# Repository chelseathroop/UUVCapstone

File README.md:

# UUVCapstone
Repository for acoustic recording device for UUV Capstone project 2015 at Portland State University.

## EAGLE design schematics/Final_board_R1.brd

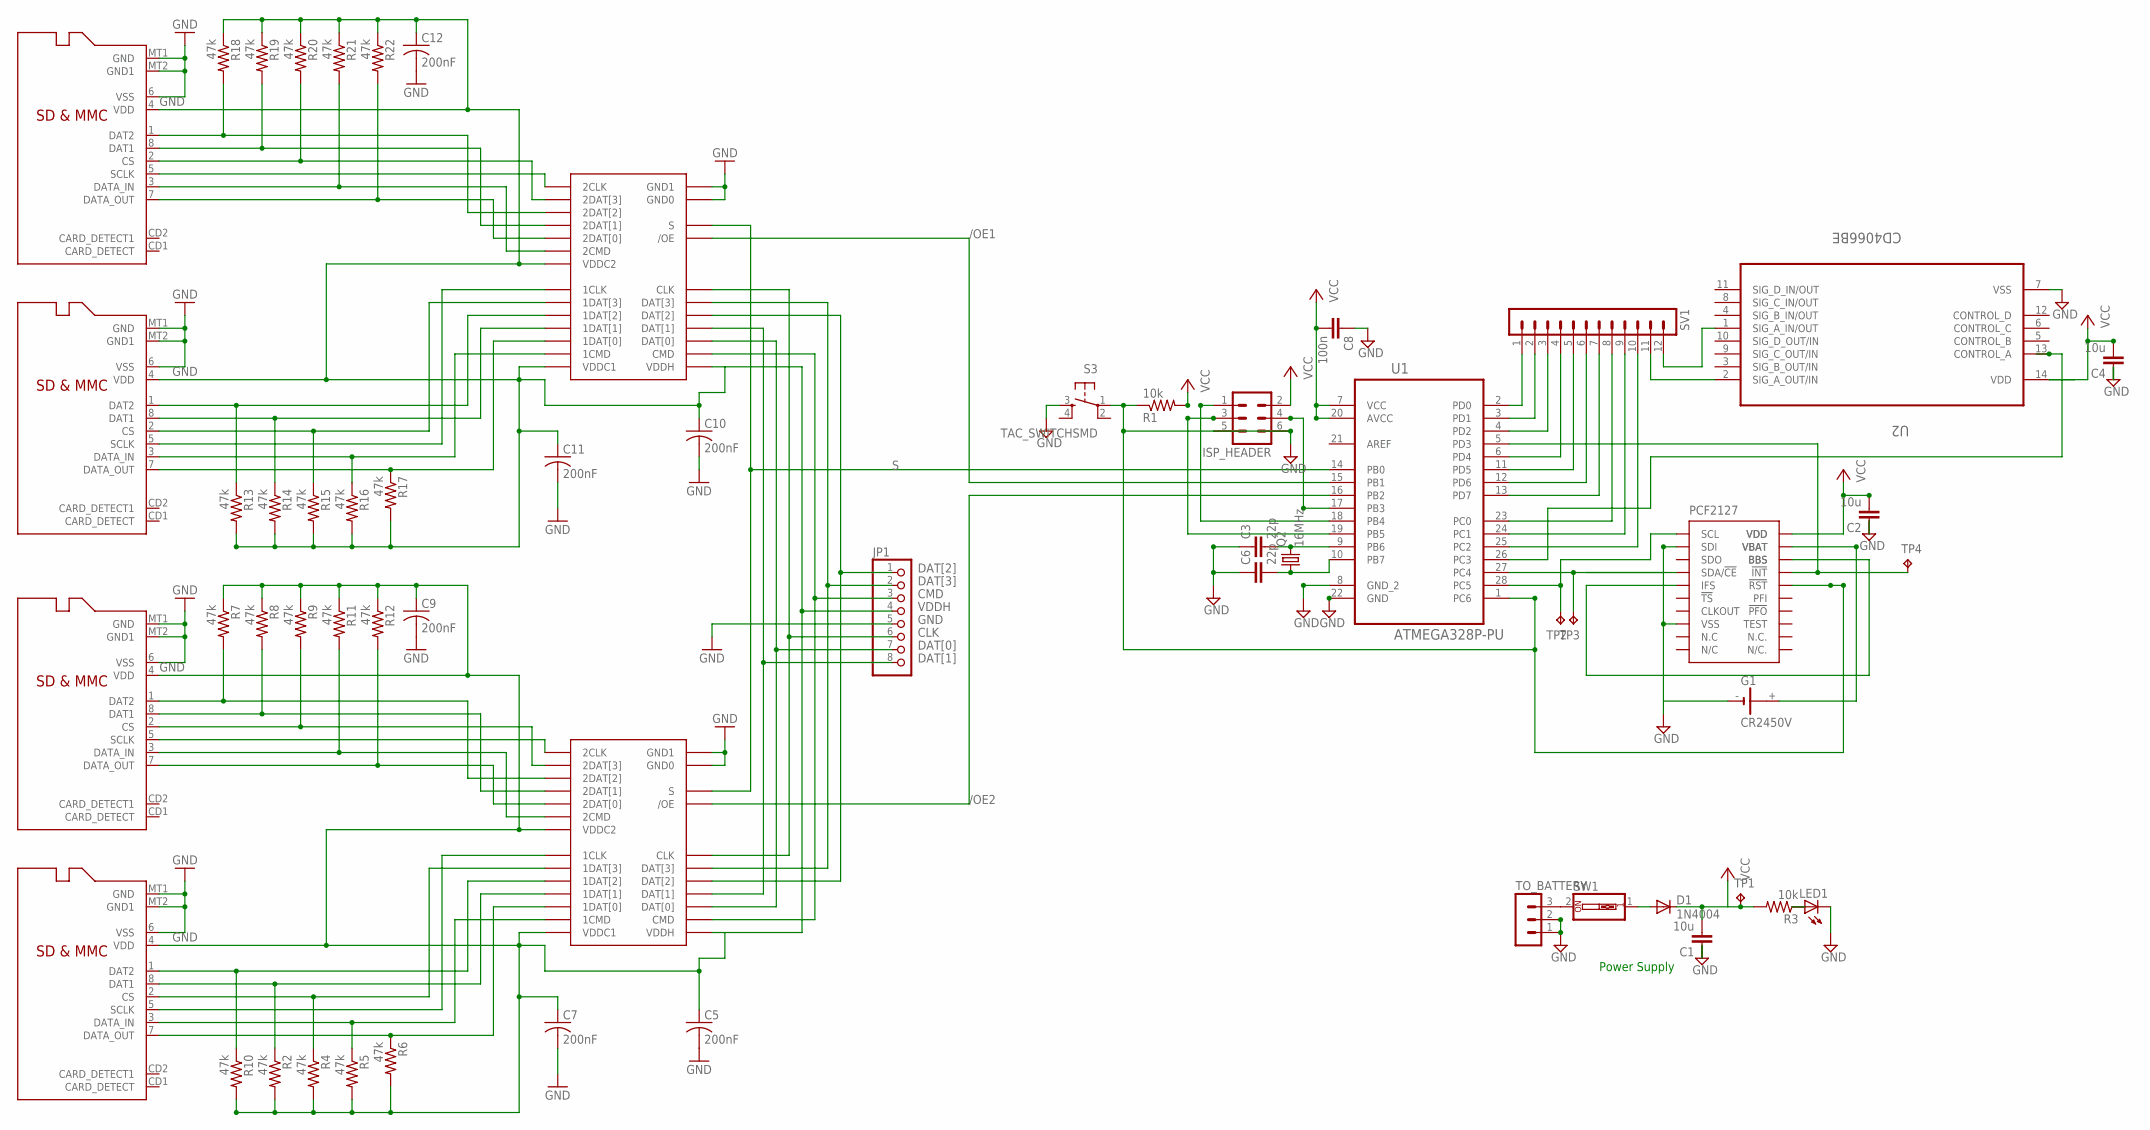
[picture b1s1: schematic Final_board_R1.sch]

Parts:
+3.6V, +3.6V1: FSSD06; MLP-24
C1, C2, C4: 10u; C0805
C3, C6: 22p; C0805
C5, C7, C9, C10, C11, C12: 200nF; C0805
C8: 100n; C0805
D1: 1N4004; DO41-10
G1: CR2450V
IC3: PCF2127; DIL18
ISP_HEADER: MA03-2
JP1: PINHD-1X8/90; 1X08/90
LED1: LEDCHIPLED_0805; CHIPLED_0805
Q2: 16MHz; HC49/S
R1, R3: 10k; R0805
R2, R4, R5, R6, R7, R8, R9, R10, R11, R12, R13, R14, R15, R16, R17, R18, R19, R20, R21, R22: 47k; R0805
S3: TAC_SWITCHSMD; TACTILE-SWITCH-SMD
SV1: MA12-1W
SW1: SW_DIP-1; EDG-01
TO_BATTERY: MA03-1
TP1, TP2, TP3, TP4: TPB1,27; B1,27
U1: ATMEGA328P-PU; DIP254P762X457-28
U2: CD4066BE; DIP254P762X508-14
USD1, USD2, USD3, USD4: MICROSD

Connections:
/OE1: +3.6V1./OE, U1.15 (PB1)
/OE2: +3.6V./OE, U1.16 (PB2)
CLK: +3.6V.CLK, +3.6V1.CLK, JP1.6
CMD: +3.6V.CMD, +3.6V1.CMD, JP1.3
DAT[0]: +3.6V.DAT[0], +3.6V1.DAT[0], JP1.7
DAT[1]: +3.6V.DAT[1], +3.6V1.DAT[1], JP1.8
DAT[2]: +3.6V.DAT[2], +3.6V1.DAT[2], JP1.1
DAT[3]: +3.6V.DAT[3], +3.6V1.DAT[3], JP1.2
GND: +3.6V.GND0, +3.6V.GND1, +3.6V1.GND0, +3.6V1.GND1, C1.1, C2.1, C3.1, C4.1, C5.2, C6.1, C7.2, C8.1, C9.2, C10.2, C11.2, C12.2, G1.-, IC3.2 (SDI), IC3.8 (VSS), IC3.14 (!RST), ISP_HEADER.5, ISP_HEADER.6, JP1.5, LED1.C, R1.1, S3.1, S3.3, TO_BATTERY.1, TO_BATTERY.2, TP3.TP, U1.1 (PC6), U1.8 (GND_2), U1.22 (GND), U1.27 (PC4), U2.7 (VSS), USD1.6 (VSS), USD1.MT1 (GND), USD1.MT2 (GND1), USD2.6 (VSS), USD2.MT1 (GND), USD2.MT2 (GND1), USD3.6 (VSS), USD3.MT1 (GND), USD3.MT2 (GND1), USD4.6 (VSS), USD4.MT1 (GND), USD4.MT2 (GND1)
unnamed: +3.6V.1DAT[0], R6.1, USD1.7 (DATA_OUT)
unnamed: LED1.A, R3.1
unnamed: D1.A, SW1.1
unnamed: C1.2, D1.C, R3.2, TP1.TP
unnamed: SV1.1, U1.2 (PD0)
unnamed: SV1.2, U1.3 (PD1)
unnamed: C3.2, Q2.2, U1.9 (PB6)
unnamed: C6.2, Q2.1, U1.10 (PB7)
unnamed: ISP_HEADER.3, U1.19 (PB5)
unnamed: SV1.3, U1.4 (PD2)
unnamed: SV1.4, U1.6 (PD4)
unnamed: IC3.1 (SCL), TP2.TP, U1.28 (PC5)
unnamed: G1.+, IC3.17 (VBAT)
unnamed: SV1.5, U1.11 (PD5)
unnamed: SV1.6, U1.12 (PD6)
unnamed: SV1.7, U1.13 (PD7)
unnamed: SV1.8, U1.23 (PC0)
unnamed: SW1.2, TO_BATTERY.3
unnamed: IC3.5 (IFS), IC3.16 (BBS)
unnamed: SV1.9, U1.24 (PC1)
unnamed: SV1.10, U1.25 (PC2)
unnamed: U1.26 (PC3), U2.13 (CONTROL_A)
unnamed: IC3.15 (!INT), TP4.TP, U1.5 (PD3)
unnamed: SV1.11, U2.2 (SIG_A_OUT/IN)
unnamed: SV1.12, U2.1 (SIG_A_IN/OUT)
unnamed: +3.6V.1DAT[1], R2.1, USD1.8 (DAT1)
unnamed: +3.6V.1DAT[2], R10.1, USD1.1 (DAT2)
unnamed: +3.6V.1CMD, R5.1, USD1.3 (DATA_IN)
unnamed: +3.6V.1CLK, USD1.5 (SCLK)
unnamed: +3.6V.2DAT[3], R9.2, USD2.2 (CS)
unnamed: +3.6V.2DAT[0], R12.2, USD2.7 (DATA_OUT)
unnamed: +3.6V.2DAT[1], R8.2, USD2.8 (DAT1)
unnamed: +3.6V.2DAT[2], R7.2, USD2.1 (DAT2)
unnamed: +3.6V.2CMD, R11.2, USD2.3 (DATA_IN)
unnamed: +3.6V.2CLCK (2CLK), USD2.5 (SCLK)
unnamed: +3.6V.1DAT[3], R4.1, USD1.2 (CS)
unnamed: +3.6V1.1DAT[0], R17.1, USD3.7 (DATA_OUT)
unnamed: +3.6V1.1DAT[1], R14.1, USD3.8 (DAT1)
unnamed: +3.6V1.1DAT[2], R13.1, USD3.1 (DAT2)
unnamed: +3.6V1.1CMD, R16.1, USD3.3 (DATA_IN)
unnamed: +3.6V1.1CLK, USD3.5 (SCLK)
unnamed: +3.6V1.2DAT[3], R20.2, USD4.2 (CS)
unnamed: +3.6V1.2DAT[0], R22.2, USD4.7 (DATA_OUT)
unnamed: +3.6V1.2DAT[1], R19.2, USD4.8 (DAT1)
unnamed: +3.6V1.2DAT[2], R18.2, USD4.1 (DAT2)
unnamed: +3.6V1.2CMD, R21.2, USD4.3 (DATA_IN)
unnamed: +3.6V1.2CLCK (2CLK), USD4.5 (SCLK)
unnamed: +3.6V1.1DAT[3], R15.1, USD3.2 (CS)
unnamed: ISP_HEADER.1, U1.18 (PB4)
unnamed: ISP_HEADER.4, U1.17 (PB3)
N.C: IC3.9 (N.C)
N/C: IC3.20 (N/C)
S: +3.6V.S, +3.6V1.S, U1.14 (PB0)
VCC: C2.2, C4.2, C8.2, IC3.18 (VDD), ISP_HEADER.2, R1.2, U1.7 (VCC), U1.20 (AVCC)
VDDH: +3.6V.VDDC1, +3.6V.VDDC2, +3.6V.VDDH, +3.6V1.VDDC1, +3.6V1.VDDC2, +3.6V1.VDDH, C5.1, C7.1, C9.1, C10.1, C11.1, C12.1, JP1.4, R2.2, R4.2, R5.2, R6.2, R7.1, R8.1, R9.1, R10.2, R11.1, R12.1, R13.2, R14.2, R15.2, R16.2, R17.2, R18.1, R19.1, R20.1, R21.1, R22.1, USD1.4 (VDD), USD2.4 (VDD), USD3.4 (VDD), USD4.4 (VDD)

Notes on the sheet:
Power Supply

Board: 2 copper layers, 57 parts (0 on the bottom side), 62 nets, no tracks yet.

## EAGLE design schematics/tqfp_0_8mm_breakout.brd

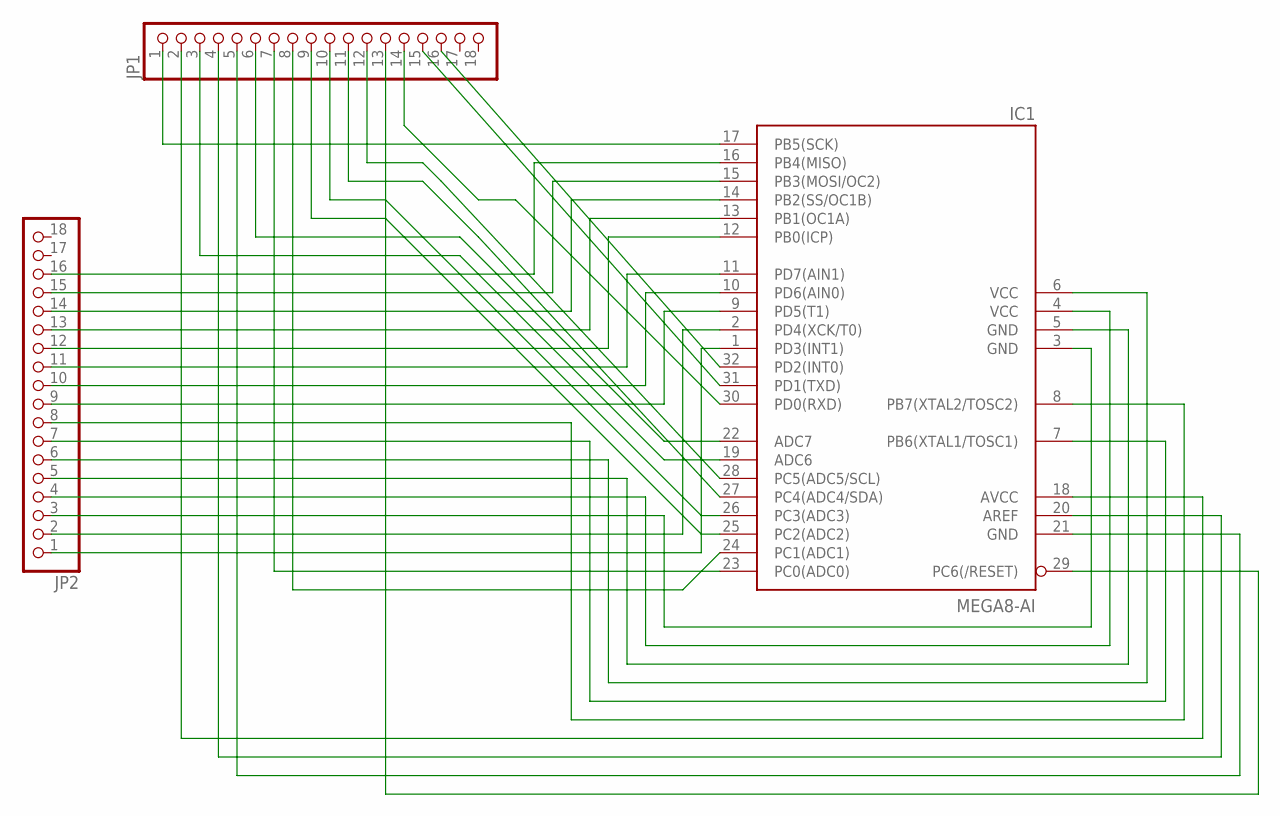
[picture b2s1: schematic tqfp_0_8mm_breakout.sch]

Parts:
IC1: MEGA8-AI; TQFP32-08
JP1, JP2: PINHD-1X18; 1X18

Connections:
unnamed: IC1.1 (PD3(INT1)), JP2.1
unnamed: IC1.2 (PD4(XCK/T0)), JP2.2
unnamed: IC1.3 (GND), JP2.3
unnamed: IC1.4 (VCC), JP2.4
unnamed: IC1.5 (GND), JP2.5
unnamed: IC1.6 (VCC), JP2.6
unnamed: IC1.7 (PB6(XTAL1/TOSC1)), JP2.7
unnamed: IC1.8 (PB7(XTAL2/TOSC2)), JP2.8
unnamed: IC1.9 (PD5(T1)), JP2.9
unnamed: IC1.10 (PD6(AIN0)), JP2.10
unnamed: IC1.11 (PD7(AIN1)), JP2.11
unnamed: IC1.12 (PB0(ICP)), JP2.12
unnamed: IC1.13 (PB1(OC1A)), JP2.13
unnamed: IC1.14 (PB2(SS/OC1B)), JP2.14
unnamed: IC1.15 (PB3(MOSI/OC2)), JP2.15
unnamed: IC1.16 (PB4(MISO)), JP2.16
unnamed: IC1.17 (PB5(SCK)), JP1.1
unnamed: IC1.18 (AVCC), JP1.2
unnamed: IC1.19 (ADC6), JP1.3
unnamed: IC1.20 (AREF), JP1.4
unnamed: IC1.21 (GND), JP1.5
unnamed: IC1.22 (ADC7), JP1.6
unnamed: IC1.23 (PC0(ADC0)), JP1.7
unnamed: IC1.24 (PC1(ADC1)), JP1.8
unnamed: IC1.25 (PC2(ADC2)), JP1.9
unnamed: IC1.26 (PC3(ADC3)), JP1.10
unnamed: IC1.27 (PC4(ADC4/SDA)), JP1.11
unnamed: IC1.28 (PC5(ADC5/SCL)), JP1.12
unnamed: IC1.29 (PC6(/RESET)), JP1.13
unnamed: IC1.30 (PD0(RXD)), JP1.14
unnamed: IC1.31 (PD1(TXD)), JP1.15
unnamed: IC1.32 (PD2(INT0)), JP1.16

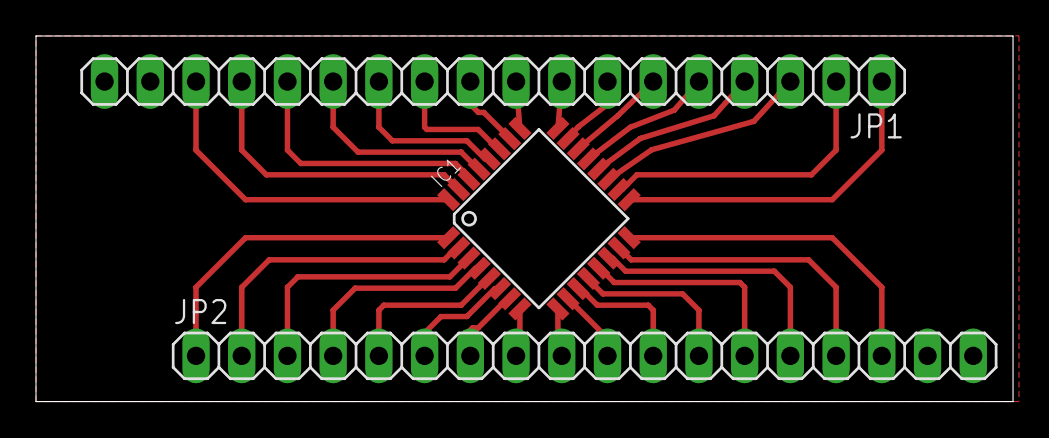
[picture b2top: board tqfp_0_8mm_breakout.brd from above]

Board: 2 copper layers, 54.3 x 20.3 mm, 3 parts (0 on the bottom side), 32 nets.

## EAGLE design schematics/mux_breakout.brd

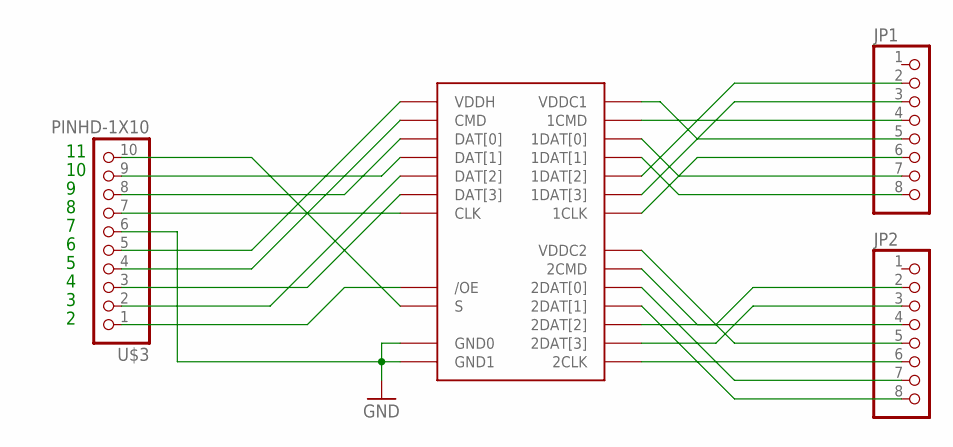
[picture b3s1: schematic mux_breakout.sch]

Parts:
JP1, JP2: PINHD-1X8CLEANBIG; 1X08-CLEANBIG
U$1: FSSD06; MLP-24
U$3: PINHD-1X10; 1X10-BIG

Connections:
1CLK: JP1.6, U$1.1CLK
1CMD: JP1.4, U$1.1CMD
1DAT[0]: JP1.7, U$1.1DAT[0]
1DAT[1]: JP1.8, U$1.1DAT[1]
1DAT[2]: JP1.2, U$1.1DAT[2]
1DAT[3]: JP1.3, U$1.1DAT[3]
2CLK: JP2.6, U$1.2CLCK (2CLK)
2CMD: JP2.4, U$1.2CMD
2DAT3: JP2.3, U$1.2DAT[3]
2DAT[0]: JP2.7, U$1.2DAT[0]
2DAT[1]: JP2.8, U$1.2DAT[1]
2DAT[2]: JP2.2, U$1.2DAT[2]
/OE: U$1./OE, U$3.1
CLK: U$1.CLK, U$3.7
CMD: U$1.CMD, U$3.4
DAT[0]: U$1.DAT[0], U$3.8
DAT[1]: U$1.DAT[1], U$3.9
DAT[2]: U$1.DAT[2], U$3.2
DAT[3]: U$1.DAT[3], U$3.3
GND: U$1.GND0, U$1.GND1, U$3.6
S: U$1.S, U$3.10
VDDC1: JP1.5, U$1.VDDC1
VDDC2: JP2.5, U$1.VDDC2
VDDH: U$1.VDDH, U$3.5

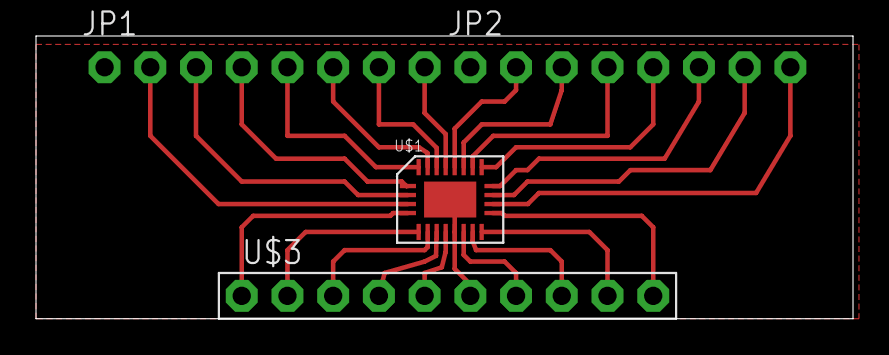
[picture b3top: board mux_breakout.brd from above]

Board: 2 copper layers, 45.4 x 15.7 mm, 4 parts (0 on the bottom side), 24 nets.

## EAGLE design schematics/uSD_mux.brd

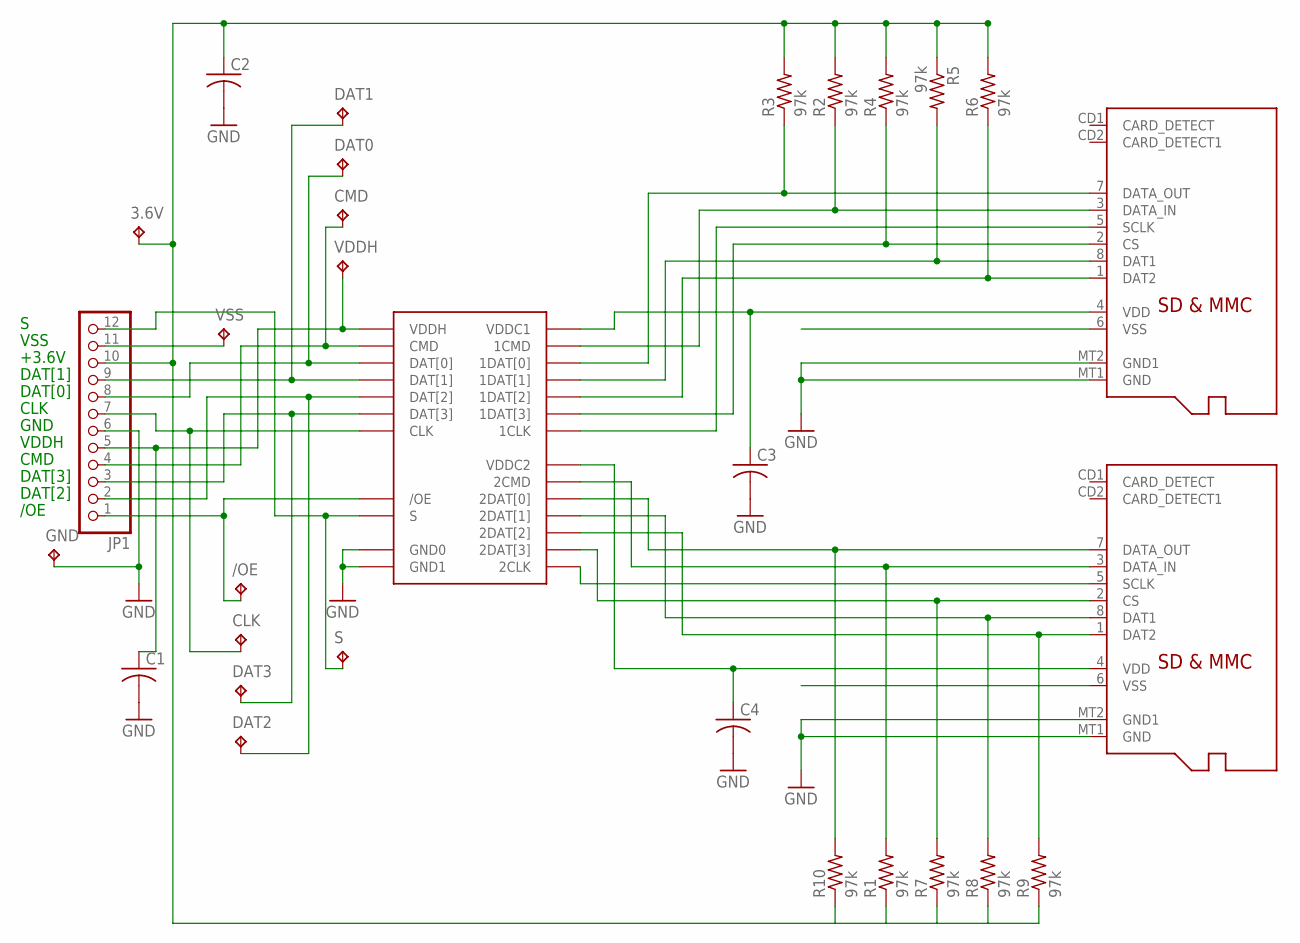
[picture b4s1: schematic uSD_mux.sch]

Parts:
3.6V: TPTP20R; TP20R
+3.6V: FSSD06; MLP-24
/OE: TPTP20R; TP20R
C1, C2, C3, C4: C-USC0805; C0805
CLK: TPTP20R; TP20R
CMD: TPTP20R; TP20R
DAT0, DAT1, DAT2, DAT3: TPTP20R; TP20R
GND: TPTP20R; TP20R
JP1: PINHD-1X12; 1X12
R1, R2, R3, R4, R5, R6, R7, R8, R9, R10: 97k; R0805
S: TPTP20R; TP20R
USD1, USD2: MICROSD
VDDH: TPTP20R; TP20R
VSS: TPTP20R; TP20R

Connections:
+3.6: 3.6V.TP, C2.1, JP1.10, R1.1, R2.2, R3.2, R4.2, R5.1, R6.2, R7.1, R8.1, R9.1, R10.1
/OE: +3.6V./OE, /OE.TP, JP1.1
CLK: +3.6V.CLK, CLK.TP, JP1.7
CMD: +3.6V.CMD, CMD.TP, JP1.4
DAT0: +3.6V.DAT[0], DAT0.TP, JP1.8
DAT1: +3.6V.DAT[1], DAT1.TP, JP1.9
DAT2: +3.6V.DAT[2], DAT2.TP, JP1.2
DAT3: +3.6V.DAT[3], DAT3.TP, JP1.3
GND: +3.6V.GND0, +3.6V.GND1, C1.2, C2.2, C3.2, C4.2, GND.TP, JP1.6, USD1.MT1 (GND), USD1.MT2 (GND1), USD2.MT1 (GND), USD2.MT2 (GND1)
unnamed: +3.6V.1DAT[3], R4.1, USD1.2 (CS)
unnamed: +3.6V.1DAT[0], R3.1, USD1.7 (DATA_OUT)
unnamed: +3.6V.1DAT[1], R5.2, USD1.8 (DAT1)
unnamed: +3.6V.1DAT[2], R6.1, USD1.1 (DAT2)
unnamed: +3.6V.1CMD, R2.1, USD1.3 (DATA_IN)
unnamed: +3.6V.1CLK, USD1.5 (SCLK)
unnamed: +3.6V.2DAT[3], R7.2, USD2.2 (CS)
unnamed: +3.6V.2DAT[0], R10.2, USD2.7 (DATA_OUT)
unnamed: +3.6V.2DAT[1], R8.2, USD2.8 (DAT1)
unnamed: +3.6V.2DAT[2], R9.2, USD2.1 (DAT2)
unnamed: +3.6V.2CMD, R1.2, USD2.3 (DATA_IN)
unnamed: +3.6V.2CLCK (2CLK), USD2.5 (SCLK)
S: +3.6V.S, JP1.12, S.TP
VDDC1: +3.6V.VDDC1, C3.1, USD1.4 (VDD)
VDDC2: +3.6V.VDDC2, C4.1, USD2.4 (VDD)
VDDH: +3.6V.VDDH, C1.1, JP1.5, VDDH.TP
VSS: JP1.11, USD1.6 (VSS), USD2.6 (VSS), VSS.TP

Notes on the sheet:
VDDH
CMD
DAT[0]
DAT[3]
DAT[2]
/OE
GND
CLK
DAT[1]
VSS
+3.6V

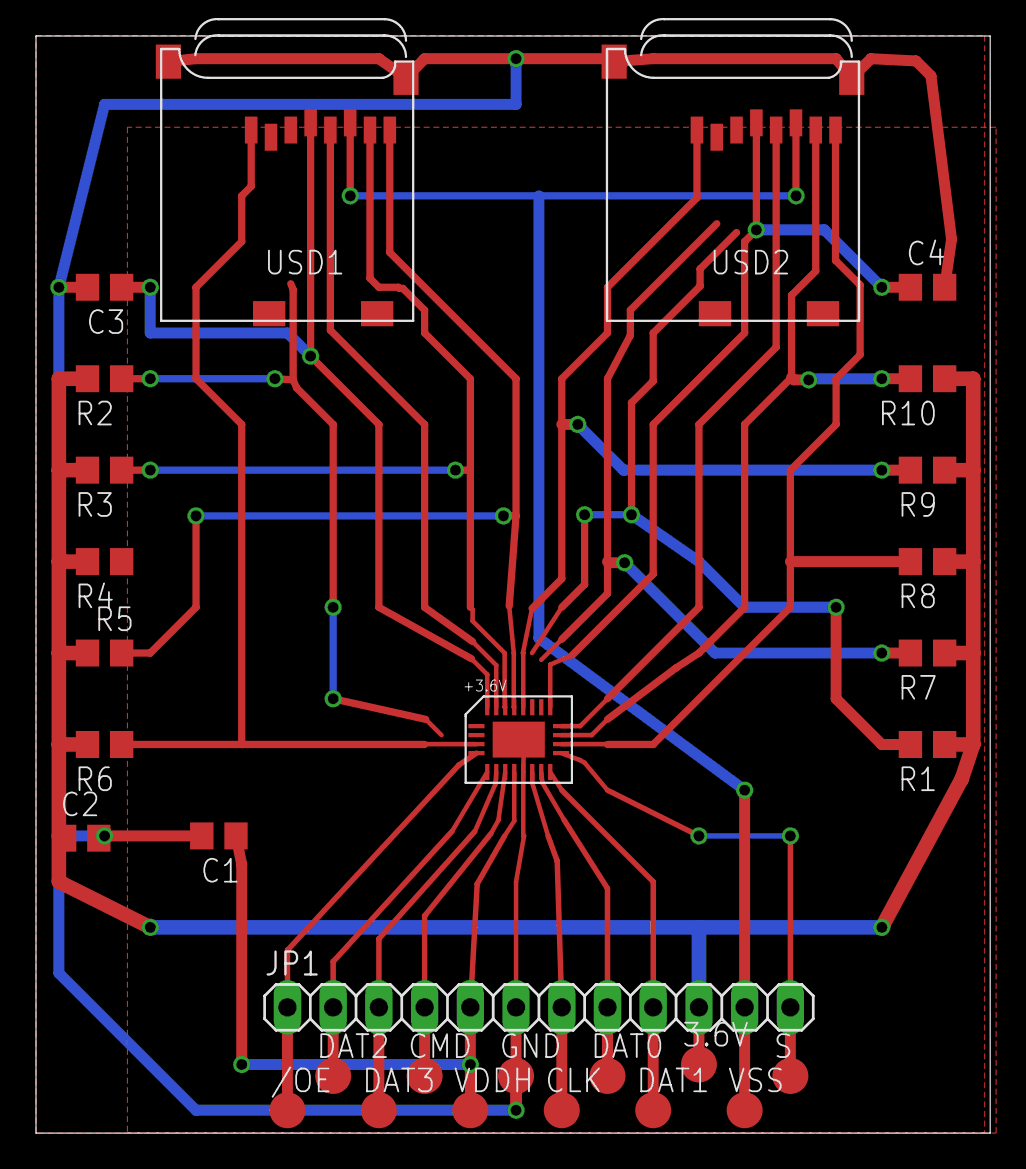
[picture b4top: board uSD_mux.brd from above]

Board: 2 copper layers, 53.0 x 61.0 mm, 30 parts (0 on the bottom side), 26 nets.

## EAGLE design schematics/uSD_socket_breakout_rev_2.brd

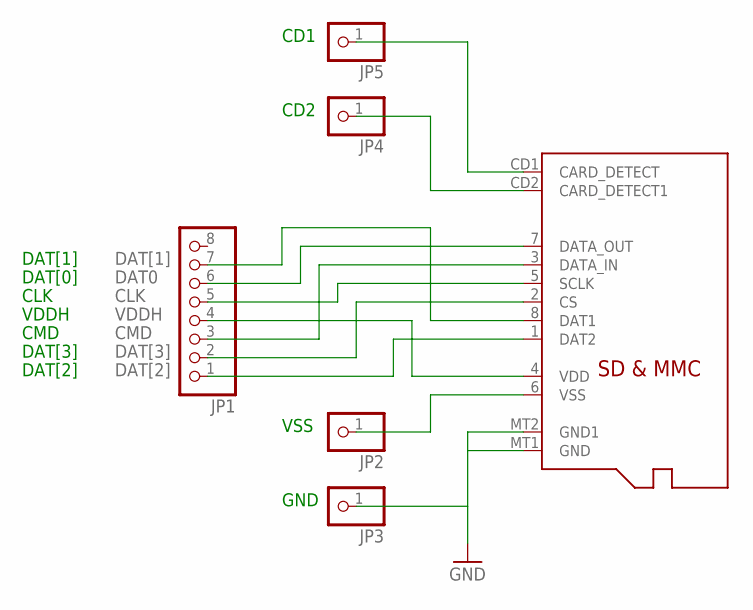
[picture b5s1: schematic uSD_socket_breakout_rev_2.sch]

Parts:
JP1: PINHD-1X8CLEANBIG; 1X08-CLEANBIG
JP2, JP3, JP4, JP5: PINHD-1X1CB; 1X01-CLEANBIG
U$1: MICROSD

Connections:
CLK: JP1.5, U$1.5 (SCLK)
CMD: JP1.3, U$1.3 (DATA_IN)
DAT0: JP1.6, U$1.7 (DATA_OUT)
DAT[1]: JP1.7, U$1.8 (DAT1)
DAT[2]: JP1.1, U$1.1 (DAT2)
DAT[3]: JP1.2, U$1.2 (CS)
GND: JP3.1, U$1.MT1 (GND), U$1.MT2 (GND1)
unnamed: JP5.1, U$1.CD1 (CARD_DETECT)
unnamed: JP4.1, U$1.CD2 (CARD_DETECT1)
VDDH: JP1.4, U$1.4 (VDD)
VSS: JP2.1, U$1.6 (VSS)

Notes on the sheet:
DAT[1]
DAT[0]
CLK
GND
VDDH
CMD
DAT[2]
CD1
CD2
DAT[3]
VSS

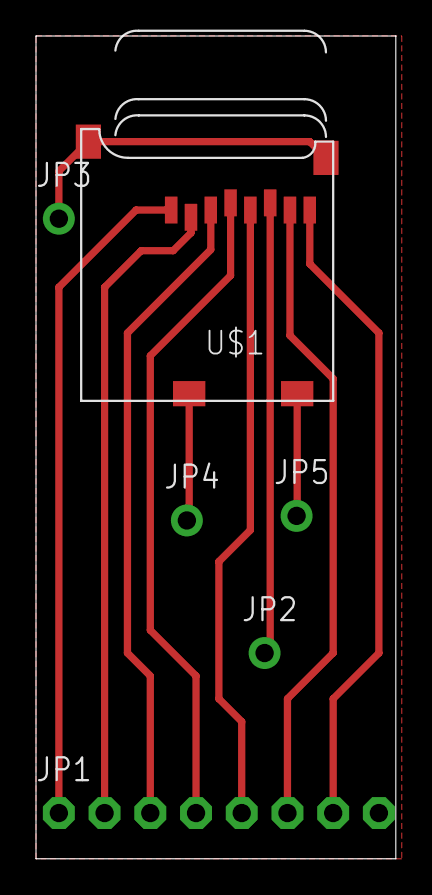
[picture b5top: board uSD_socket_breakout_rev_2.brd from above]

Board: 2 copper layers, 20.0 x 45.7 mm, 6 parts (0 on the bottom side), 11 nets.

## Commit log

2015-01-10 Adding initial UUV capstone proposal given to ECE department
2015-01-13 Adding meeting minutes folder
2015-01-14 Adding folder for assignments to be completed for capstone project, began proposal document
2015-01-15 Edited Capstone Proposal and added the meeting minutes
2015-01-21 Software algorithm R1.0 version
2015-01-22 Adding meeting minutes from last night and Powerpoint template for proposal
2015-01-22 Updating powerpoint template for everyone to add their sections to
2015-01-23 Added Phu's slides to pp
2015-01-23 Added Trevors pp slides and meeting minute start
2015-01-23 Uploading photos for powerpoint, relevent document, and meeting minutes
2015-01-23 Create test
2015-01-24 Updated power point with notes from meeting and added Phu's updates
2015-01-26 Added button interface slide
2015-01-26 Added Trevor and Saidas slides
2015-01-26 Added some photos to pp
2015-01-26 Added pdf version of pp
2015-01-26 Deleted uneccessary slide
2015-01-26 Updated Saidas slide
2015-01-26 Rearranged and editted slides
2015-01-26 Added block diagram
2015-01-26 SAved current pdf
2015-01-26 Added project schedule to slides
2015-01-27 Testing commit from trevors pc
2015-01-27 Preliminary Power Budget for Daughterboard
2015-02-05 2-4-15 meeting notes
2015-02-17 mux circuit and relevant datasheets
    Datasheets of components used in MUX circuit. Schematics not yet
    finalized, need some review before sending to oshpark.
2015-02-18 Added document addressing concerns about SD socket connector
2015-02-19 Added folder section to comment on current issues and relevant comments.
2015-02-19 Moved this file to issuesandcomments file
2015-02-21 Update new revision of software algorithm and add software diagram file
2015-02-21 Code
    TWI_MASTER.C
2015-02-21 RTC_MCU_CODE
    RTC and MCU communication
2015-02-21 Revert "Code"
    This reverts commit 0a320a8a4ce39f85cd705e5057287788313ad082.
2015-02-24 Updated uSD mux board
2015-02-24 Added button sequence for changing sample rate and recording
2015-02-24 Updated uSD mux board layout
    Forgot to check oshpark DRU before committing first time. Made
    revisions necessary to board layout to meet oshparks design rules.
2015-02-24 Updated uSD mux sch/brd files
    Added decoupling capacitors, labeled +3.6V connection on 12 pin
    connector.
2015-02-25 Updated uSD board layout
    Board was excessively expensive, changed board layout to reduce surface
    area --> cheaper fab . Previous iteration was quoted $37 at oshpark,
    updated board $25.
2015-02-26 uSD socket breakout board
2015-03-02 High Level Algorithm
    MCU_RTC High Level Algorithm
2015-03-02 Calculation
    File Size Calculation
2015-03-02 Post mission GUI R2.0
2015-03-02 MCU and RTC interface circuit diagram Revision R1.0
2015-03-25 Uploaded the updated revision of Post-mission GUI
2015-03-27 updated GUI - adjusted the display size
2015-03-27 updated RTC-MCU schematic : implemented CMOS as switches for button services. Uploaded on 03/27/15
2015-03-27 RTC CODE
    RTC ROUTINE and RTC _MCU_CODE
2015-03-31 Service button code revision 1. Posted 033015
2015-03-31 Updated_RTC_MCU_MUX_Button
    Software_RTC_MCU_MUX_Button
2015-04-03 sample_input_file
    Sample input file
2015-04-05 Added integrated circuit template and BOM
2015-04-09 TQFP-32-08 breakout board
    Drafted breakout board for atmega168a tqfp 0.8mm pitch for Phu
2015-04-09 MLP-24 breakout board
    Breakout board for FSSD06 w/ MLP-24 package.
2015-04-10 seaglider.c and seaglider.h
    corrected seaglider.c and seaglider.h
2015-04-11 Breakout boards for MUX and uSD socket, updated mux+uSD schematic
    Built individual breakout boards for MUX chip and uSD socket.
    Discovered errors in MUX and uSD integrated board and updated
    schematic--ripped up wrong connections in .brd file but did not bother
    rerouting traces since this board will most likely not be fabbed again.
2015-04-13 Added the example for data format from pre-mission software
2015-04-17 Added sd slot datasheet for reference
2015-04-20 Updated sample for file generated by pre-mission software
2015-04-20 Code to test when passing data from file to loop
2015-04-29 Added current premission software version
2015-04-30 Updating premission software
2015-05-01 Made some changes so this is a working copy
2015-05-03 updated software
2015-05-05 Changed syntax of application to have classes for entry validation
2015-05-13 Adding current version of application with first implementation of error checking
2015-05-13 Added error checking for all entries
2015-05-14 Added SD car file counts for Phu
2015-05-14 Updated circuitry for MCU-RTC-BUTTON SERVICE interface
2015-05-15 final schematic/board layout
    Schematic is done, working on board layout, this may take a few days for
    me to complete.
2015-05-24 Prelim Layout Complete
    Completed first board layout in eagle cad. Needs revision.
2015-05-24 test sample
2015-05-25 Uploaded new layout for routing
    Had to rework board layout to accommodate current LPKF router
    functionality(2 tooling slots out of order, limited to max 10 instead of
    12 tools for job). I'm including gerber files from CAM processing. The
    top, bottom, outline .gbx files are needed, as well as the .xln drill
    file, to import into the routing program.
2015-05-25 Updated rough drat of Captsone Poster
2015-05-26 Updated poster
2015-05-26 Udate poster
2015-05-26 Update Poster
2015-05-28 Uploaded integrated software and UUV.h file
2015-05-31 updated pictures
2015-06-03 latest version of program
2015-06-05 Uploaded latest version of integrated software
2015-06-05 Test Plan
    Added Test Plan
2015-06-10 latest version of premission software
2015-06-10 Updated software- highlighted filepath
2015-06-11 Testcode
    Testcode
2015-06-11 Final_Test_Code
    Final Test Code
2015-06-11 Final Test Code
    Final Test Code(post mission)

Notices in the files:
parts and their libraries:
SparkFun-Electromechanical: Licensing: Creative Commons ShareAlike 4.0 International - https://creativecommons.org/licenses/by-sa/4.0
